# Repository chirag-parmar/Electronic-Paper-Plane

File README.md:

# Electronic-Paper-Plane
As the name suggests the key idea of the project is to propel a paper airplane using electronic motors. this i sdone using a ESP8266 and transistors to control the motors over wifi. The communication over wifi takes place by using the ESP8266 as a HTTP Server. 
Files include the control board design. - made on eagle.

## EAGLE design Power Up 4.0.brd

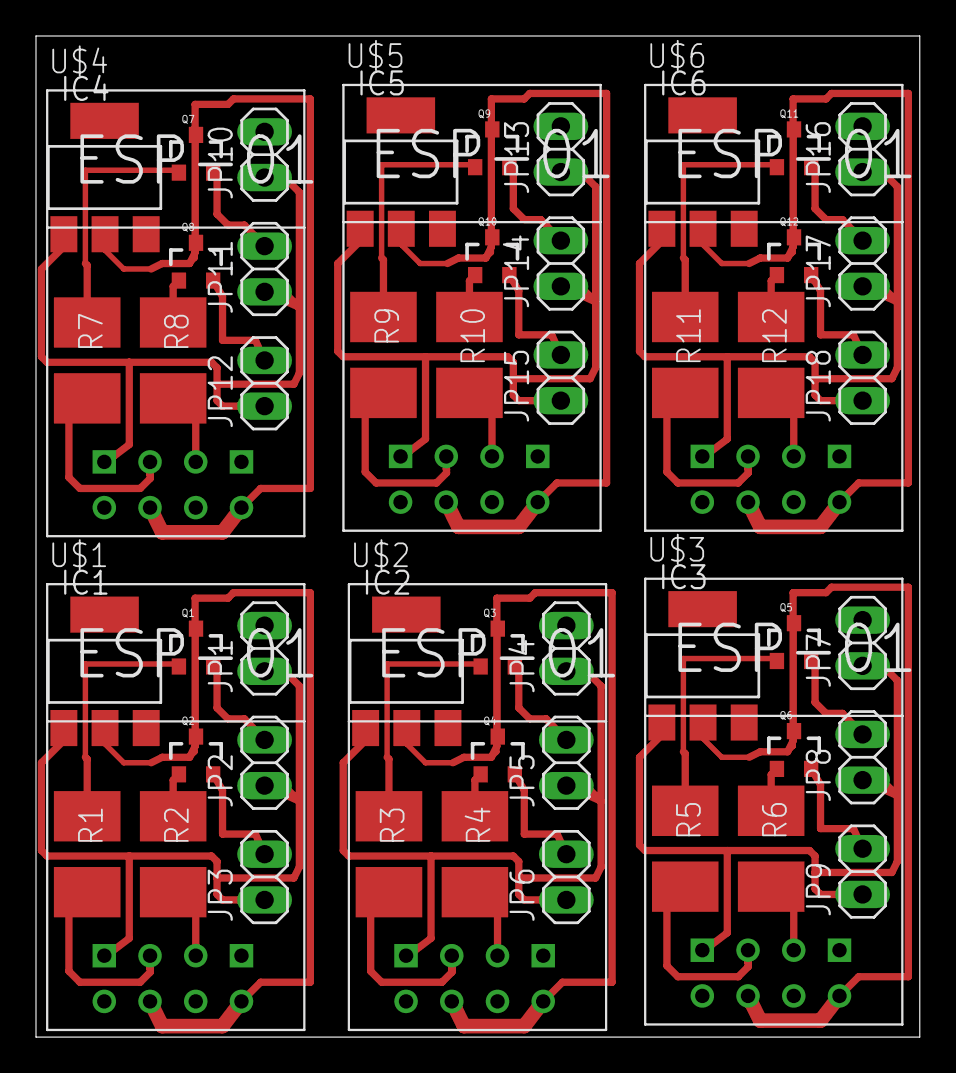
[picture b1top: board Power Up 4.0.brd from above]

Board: 2 copper layers, 49.1 x 55.6 mm, 54 parts (0 on the bottom side), 54 nets.

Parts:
IC1, IC2, IC3, IC4, IC5, IC6: REG1117; SOT223
JP1, JP4, JP7, JP10, JP13, JP16: Power; 1X02
JP2, JP5, JP8, JP11, JP14, JP17: M1; 1X02
JP3, JP6, JP9, JP12, JP15, JP18: M2; 1X02
Q1, Q2, Q3, Q4, Q5, Q6, Q7, Q8, Q9, Q10, Q11, Q12: MPSA42; SOT23-3
R1, R2, R3, R4, R5, R6, R7, R8, R9, R10, R11, R12: SMS-WAV
U$1, U$2, U$3, U$4, U$5, U$6: ESP01

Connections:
unnamed: Q1.1, R1.2
unnamed: Q2.1, R2.2
unnamed: IC1.1, JP1.1, JP2.1, JP3.1, U$1.GND
unnamed: IC1.2, Q1.3, Q2.3, U$1.CH_PD, U$1.VCC
unnamed: IC1.3, JP1.2
unnamed: R1.1, U$1.GPIO2
unnamed: R2.1, U$1.GPIO0
unnamed: JP2.2, Q1.2
unnamed: JP3.2, Q2.2
unnamed: IC2.1, JP4.1, JP5.1, JP6.1, U$2.GND
unnamed: IC2.2, Q3.3, Q4.3, U$2.CH_PD, U$2.VCC
unnamed: IC2.3, JP4.2
unnamed: Q3.1, R3.2
unnamed: Q4.1, R4.2
unnamed: R3.1, U$2.GPIO2
unnamed: R4.1, U$2.GPIO0
unnamed: JP5.2, Q3.2
unnamed: JP6.2, Q4.2
unnamed: IC3.1, JP7.1, JP8.1, JP9.1, U$3.GND
unnamed: IC3.2, Q5.3, Q6.3, U$3.CH_PD, U$3.VCC
unnamed: IC3.3, JP7.2
unnamed: Q5.1, R5.2
unnamed: Q6.1, R6.2
unnamed: R5.1, U$3.GPIO2
unnamed: R6.1, U$3.GPIO0
unnamed: JP8.2, Q5.2
unnamed: JP9.2, Q6.2
unnamed: IC4.1, JP10.1, JP11.1, JP12.1, U$4.GND
unnamed: IC4.2, Q7.3, Q8.3, U$4.CH_PD, U$4.VCC
unnamed: IC4.3, JP10.2
unnamed: Q7.1, R7.2
unnamed: Q8.1, R8.2
unnamed: R7.1, U$4.GPIO2
unnamed: R8.1, U$4.GPIO0
unnamed: JP11.2, Q7.2
unnamed: JP12.2, Q8.2
unnamed: IC5.1, JP13.1, JP14.1, JP15.1, U$5.GND
unnamed: IC5.2, Q9.3, Q10.3, U$5.CH_PD, U$5.VCC
unnamed: IC5.3, JP13.2
unnamed: Q9.1, R9.2
unnamed: Q10.1, R10.2
unnamed: R9.1, U$5.GPIO2
unnamed: R10.1, U$5.GPIO0
unnamed: JP14.2, Q9.2
unnamed: JP15.2, Q10.2
unnamed: IC6.1, JP16.1, JP17.1, JP18.1, U$6.GND
unnamed: IC6.2, Q11.3, Q12.3, U$6.CH_PD, U$6.VCC
unnamed: IC6.3, JP16.2
unnamed: Q11.1, R11.2
unnamed: Q12.1, R12.2
unnamed: R11.1, U$6.GPIO2
unnamed: R12.1, U$6.GPIO0
unnamed: JP17.2, Q11.2
unnamed: JP18.2, Q12.2

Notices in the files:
parts and their libraries:
SparkFun-DiscreteSemi: Licensing: Creative Commons ShareAlike 4.0 International - https://creativecommons.org/licenses/by-sa/4.0
